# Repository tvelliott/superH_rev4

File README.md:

<html>
<b>High-performance narrow-band receiver hardware.</b>
<BR>
<BR><B>SuperH_rev4</B>
<BR>
<p>

<BR>
<BR>
<BR>

<BR>To compile:
<BR>install the gcc arm toolchain version gcc-arm-none-eabi-7-2018-q2-update/
<BR>https://developer.arm.com/tools-and-software/open-source-software/developer-tools/gnu-toolchain/gnu-rm/downloads/7-2018-q2-update
<BR>
<BR>In the firmware directory, create a symbolic link to the toolchain:
<BR>e.g. ln -s ../gcc-arm-none-eabi-7-2018-q2-update arm-toolchain
<BR>Then type 'make' 
<BR><BR>
The firmware can decode the follow protocols in stand-alone mode (NO PC):
<PRE>
Available SuperH+ built-in/stand-alone demod/decoders
------------------
FM Analog narrow/med/wide (mode fm)
AM Analog narrow/med/wide (mode am)
IQ 16-bit over UDP (mode iq) + GNURadio Driver
P25P1 Voice + Trunking Control Channel (mode p25)
DMR Voice + ConnectPlus Trunking Control Channel (mode dmr)
ADSB Mode-S - Console output (mode adsb)   This mode uses 2 separate ADCs in single ended mode with 2 Msps / 8-bit.
ACARS - Console output (mode acars)
FLEX-4FSK-1600 - Console output (mode pagers, fm)
POCSAG 1200 - Console output (mode pagers, fm)
</PRE>
<BR>
<BR>

1st IF is 1.5 GHz  (high IF like a typical spectrum analyzer)
<BR><BR>
Baseband filters are 10 - 150 kHz in 16 steps.  70dB adjacent rejection,  100+ dB alternate rejection.
<BR><BR>NCO based final tuning.
<BR><BR>20dB pre-LNA step-attenuator front-end (controlled by AGC)
<BR><BR>AGC + DSP extends dynamic range to over 150dB.
<BR><BR>ACARS receives long messages >350 miles away with an indoor antenna and 0 bit errors.
<BR><BR>DC coupling and extremely stable TCXO makes sub-Hz demodulation with software-based DC offset correction possible
<BR><BR>I/Q ADCs SNR is >= 82 dB in 16-bit differential mode of operation (10-150 kHz baseband filter mode).   

<BR>
<BR>
<a href="https://github.com/tvelliott/superH_rev4/blob/master/audio_samples/superH_fm_radio_dynamics_silence_demo.wav">superH_fm_radio_dynamics_silence_demo.wav (recorded off air)</a>
<BR>
<BR>
superH FM demod demonstration   
https://youtu.be/HBXcUFW8yaA  
<BR><BR>
P25P1 demo
https://youtu.be/G3MCHvNcKHg
<BR><BR>
superH gqrx / 40-meter / AM demo
https://youtu.be/u9L5sJRPFiQ
<BR><BR>
Local ham radio repeater VHF
https://youtu.be/9KYXXc-55yA
<BR><BR>
SuperH+ receiving ADSB
https://youtu.be/LvIR2hlR7_A
<BR><BR>
<BR>

<BR>
</html>

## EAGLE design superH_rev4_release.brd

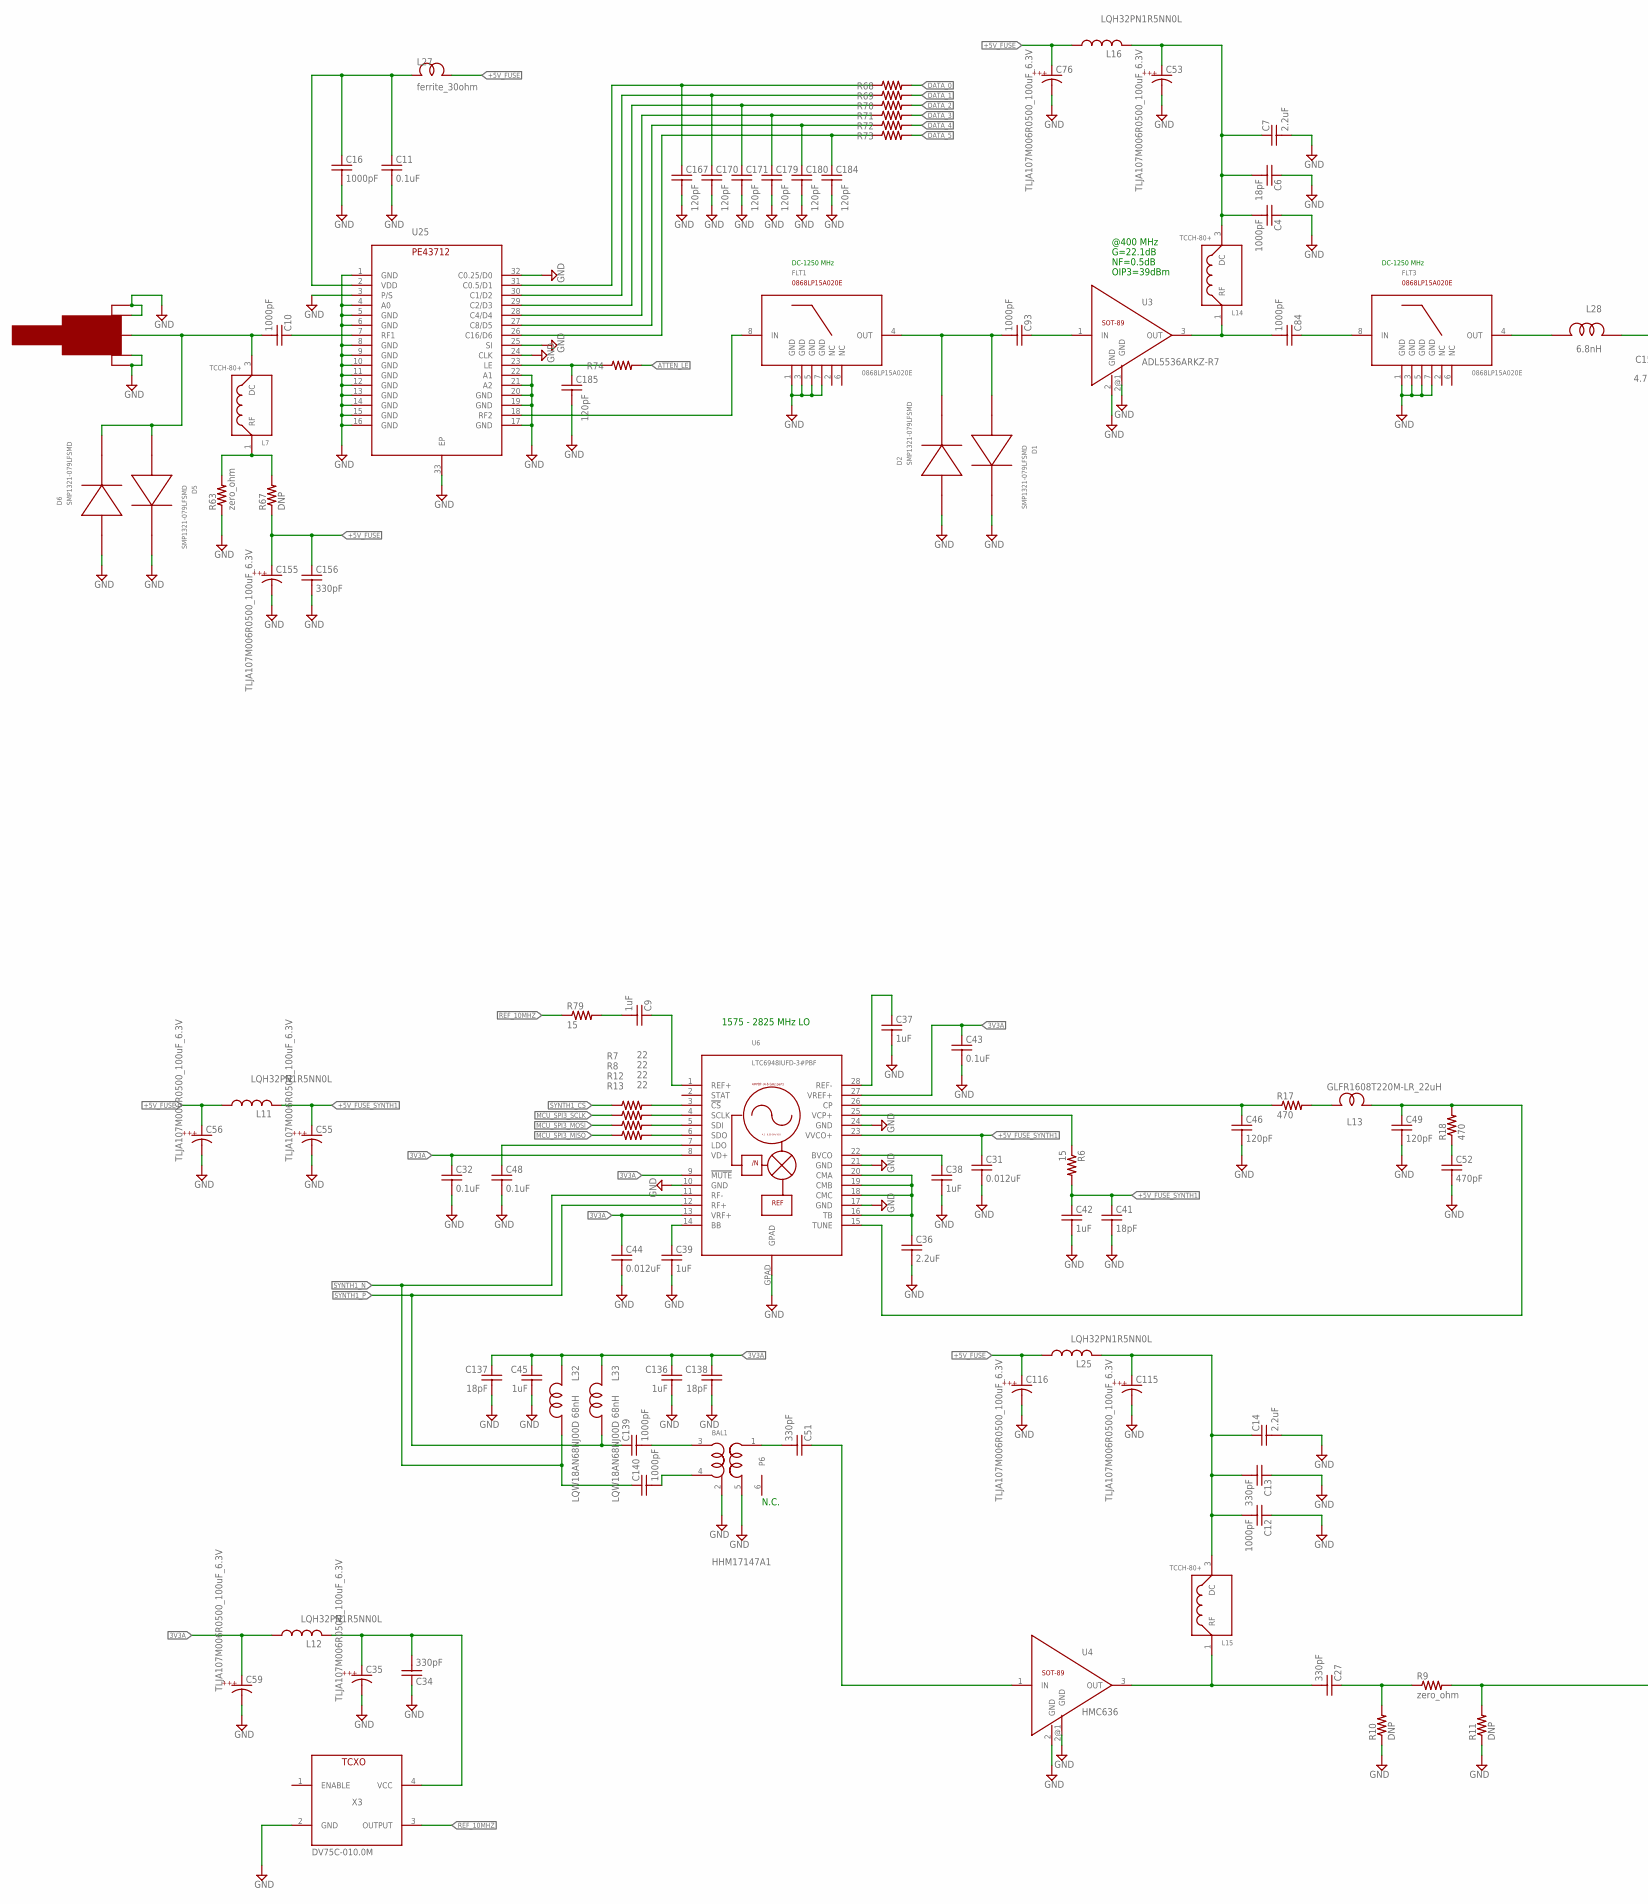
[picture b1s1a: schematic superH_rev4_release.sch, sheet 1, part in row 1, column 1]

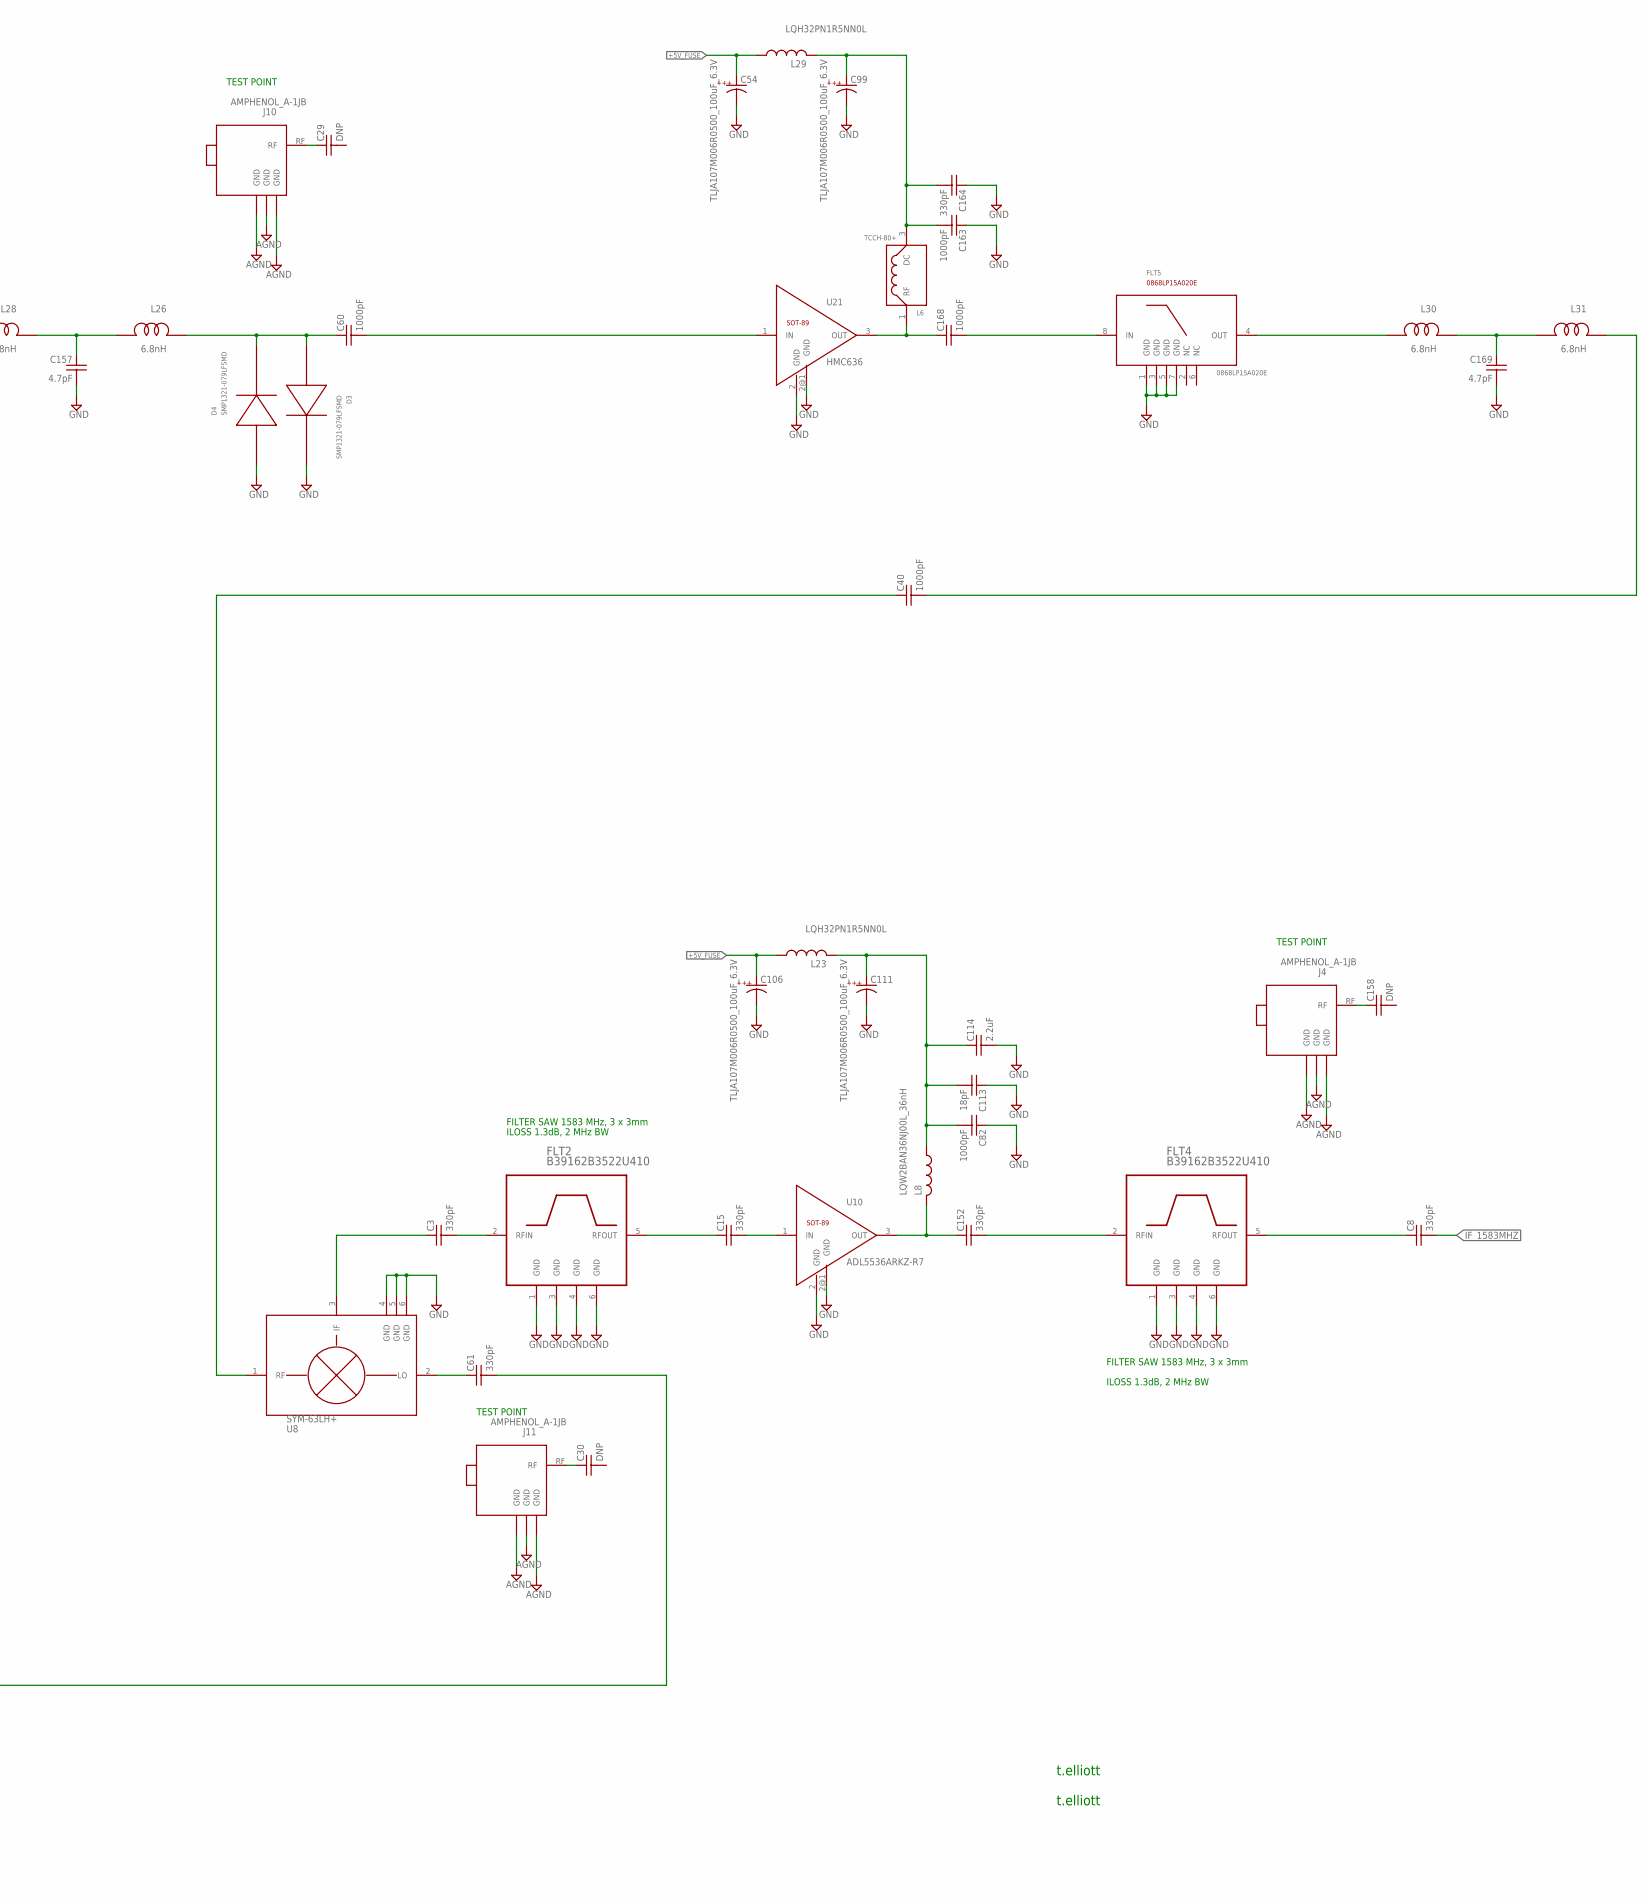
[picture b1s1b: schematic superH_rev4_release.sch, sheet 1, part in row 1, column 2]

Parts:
BAL1: HHM17147A1; TDK_BALUN_5PIN
C3, C8, C13, C15, C27, C34, C51, C61, C152, C156, C164: 330pF; C0603
C4, C10, C12, C40, C60, C82, C84, C93, C163, C168: 1000pF; C0603
C6, C113, C137, C138: 18pF; C0603
C7, C14, C36, C114: 2.2uF; C0603
C9, C45, C136: 1uF; C0603
C11, C32, C43, C48: 0.1uF; C0402
C16, C139, C140: 1000pF; C0402
C29, C30, C158: DNP; C0603
C31, C44: 0.012uF; C0402
C35, C53, C54, C55, C56, C59, C76, C99, C106, C111, C115, C116, C155: TLJA107M006R0500_100uF_6.3V; 1210K
C37, C38, C39, C42: 1uF; C0402
C41: 18pF; C0402
C46, C49, C167, C170, C171, C179, C180, C184, C185: 120pF; C0402
C52: 470pF; C0402
C157, C169: 4.7pF; C0603
D1, D2, D3, D4, D5, D6: SMP1321-079LFSMD; SC-79_PINDIODE
FLT1, FLT3, FLT5: 0868LP15A020E; LPF_0868LP15A020
FLT2, FLT4: B39162B3522U410; SM3030-6
J3: SMA0.062; SMA_EDGE
J4, J10, J11: AMPHENOL_A-1JB; UFLCONNECTOR
L6, L7, L14, L15: TCCH-80+
L8: LQW2BAN36NJ00L_36nH; L2012C; PARTNUMBER ELJ-PA331KF
L11, L12, L16, L23, L25, L29: LQH32PN1R5NN0L; L3225M; PARTNUMBER ELJ-PA331KF
L13: GLFR1608T220M-LR_22uH; 0603
L26, L28, L30, L31: 6.8nH; MURATA_LQW_0603
L27: ferrite_30ohm; 0603
L32, L33: LQW18AN68NJ00D 68nH; MURATA_LQW_0603
R6, R68, R69, R70, R71, R72, R73, R74, R79: 15; R0402
R7, R8, R12, R13: 22; R0603_COMPACT
R9: zero_ohm; R0603
R10, R11: DNP; R0603
R17, R18: 470; R0402
R63: zero_ohm; R1206
R67: DNP; R1206
U3, U10: ADL5536ARKZ-R7; SOT89
U4, U21: HMC636; SOT89
U6: LTC6948IUFD-3#PBF; QFN28_NONSQ
U8: SYM-63LH+; SYM-18H
U25: PE43712SMD; QFN32
X3: DV75C-010.0M; CWX8XX_5MM_7MM

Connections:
3V3A: C32.1, C43.1, C44.1, C45.1, C59.A, C136.1, C137.1, C138.1, L12.1, L32.2, L33.2, U6.8 (VD+), U6.9 (!MUTE), U6.13 (VRF+), U6.27 (VREF+); also elsewhere on the board
+5V_ATTEN: C11.1, C16.1, L27.1, U25.2 (VDD)
+5V_FUSE: C54.A, C56.A, C76.A, C106.A, C116.A, C155.A, C156.1, L11.1, L16.1, L23.1, L25.1, L27.2, L29.1, R67.1; also elsewhere on the board
+5V_FUSE_SYNTH1: C31.1, C41.1, C42.1, C55.A, L11.2, R6.2, U6.23 (VVCO+)
ATTEN_LE: R74.2; also elsewhere on the board
BALUN_N: BAL1.4 (BP1), C140.2
BALUN_P: BAL1.3 (BP2), C139.2
D0: C167.1, R68.1, U25.31 (C0.5/D1)
D1: C170.1, R69.1, U25.30 (C1/D2)
D2: C171.1, R70.1, U25.29 (C2/D3)
D3: C179.1, R71.1, U25.28 (C4/D4)
D4: C180.1, R72.1, U25.27 (C8/D5)
D5: C184.1, R73.1, U25.26 (C16/D6)
DATA_0: R68.2; also elsewhere on the board
DATA_1: R69.2; also elsewhere on the board
DATA_2: R70.2; also elsewhere on the board
DATA_3: R71.2; also elsewhere on the board
DATA_4: R72.2; also elsewhere on the board
DATA_5: R73.2; also elsewhere on the board
GND: BAL1.2 (FEED), BAL1.5 (GND), C4.1, C6.1, C7.2, C11.2, C12.1, C13.1, C14.2, C16.2, C31.2, C32.2, C34.1, C35.C, C36.2, C37.2, C38.2, C39.2, C41.2, C42.2, C43.2, C44.2, C45.2, C46.2, C48.2, C49.2, C52.2, C53.C, C54.C, C55.C, C56.C, C59.C, C76.C, C82.1, C99.C, C106.C, C111.C, C113.1, C114.2, C115.C, C116.C, C136.2, C137.2, C138.2, C155.C, C156.2, C157.2, C163.1, C164.1, C167.2, C169.2, C170.2, C171.2, C179.2, C180.2, C184.2, C185.2, D1.C, D2.A, D3.C, D4.A, D5.C, D6.A, FLT1.1 (GND), FLT1.3 (GND), FLT1.5 (GND), FLT1.7 (GND), FLT2.1 (GND), FLT2.3 (GND), FLT2.4 (GND), FLT2.6 (GND), FLT3.1 (GND), FLT3.3 (GND), FLT3.5 (GND), FLT3.7 (GND), FLT4.1 (GND), FLT4.3 (GND), FLT4.4 (GND), FLT4.6 (GND), FLT5.1 (GND), FLT5.3 (GND), FLT5.5 (GND), FLT5.7 (GND), J3.GND@1 (GND), J3.GND@2 (GND), J3.GND@3 (GND), J3.GND@4 (GND), J4.1 (GND), J4.2 (GND), J4.3 (GND), J10.1 (GND), J10.2 (GND), J10.3 (GND), J11.1 (GND), J11.2 (GND), J11.3 (GND), R10.1, R11.1, R63.1, U3.2 (GND), U3.2@1 (GND), U4.2 (GND), U4.2@1 (GND), U6.10 (GND), U6.17 (GND), U6.21 (GND), U6.24 (GND), U6.GPAD, U8.4 (GND), U8.5 (GND), U8.6 (GND), U10.2 (GND), U10.2@1 (GND), U21.2 (GND), U21.2@1 (GND), U25.1 (GND), U25.3 (P/S), U25.4 (A0), U25.5 (GND), U25.6 (GND), U25.8 (GND), U25.9 (GND), U25.10 (GND), U25.11 (GND), U25.12 (GND), U25.13 (GND), U25.14 (GND), U25.15 (GND), U25.16 (GND), U25.17 (GND), U25.19 (GND), U25.20 (GND), U25.21 (A2), U25.22 (A1), U25.24 (CLK), U25.25 (SI), U25.32 (C0.25/D0), U25.33 (EP), X3.2 (GND); also elsewhere on the board
IF_1583MHZ: C8.2; also elsewhere on the board
LE: C185.1, R74.1, U25.23 (LE)
MCU_SPI3_MISO: R13.1; also elsewhere on the board
MCU_SPI3_MOSI: R12.1; also elsewhere on the board
MCU_SPI3_SCLK: R8.1; also elsewhere on the board
unnamed: C152.2, FLT4.2 (RFIN)
unnamed: C84.2, L14.1 (RF), U3.3 (OUT)
unnamed: C82.2, C111.A, C113.2, C114.1, L8.1, L23.2
unnamed: C60.1, D3.A, D4.C, L26.2
unnamed: C27.2, L15.1 (RF), U4.3 (OUT)
unnamed: C29.1, J10.RF
unnamed: C30.1, J11.RF
unnamed: C15.1, FLT2.5 (RFOUT)
unnamed: C3.2, FLT2.2 (RFIN)
unnamed: C51.1, U4.1 (IN)
unnamed: C15.2, U10.1 (IN)
unnamed: C9.1, U6.1 (REF+)
unnamed: C27.1, R9.1, R10.2
unnamed: C61.2, R9.2, R11.2
unnamed: C4.2, C6.2, C7.1, C53.A, L14.3 (DC), L16.2
unnamed: C8.1, FLT4.5 (RFOUT)
unnamed: FLT1.8 (IN), U25.18 (RF2)
unnamed: C99.A, C163.2, C164.2, L6.3 (DC), L29.2
unnamed: C37.1, U6.28 (REF-)
unnamed: C36.1, U6.16 (TB), U6.18 (CMC), U6.19 (CMB), U6.20 (CMA)
unnamed: C38.1, U6.22 (BVCO)
unnamed: C39.1, U6.14 (BB)
unnamed: R6.1, U6.25 (VCP+)
unnamed: C48.1, U6.7 (LDO)
unnamed: C46.1, R17.1, U6.26 (CP)
unnamed: C61.1, U8.2 (LO)
unnamed: C93.1, U3.1 (IN)
unnamed: BAL1.1 (UBAL), C51.2
unnamed: C52.1, R18.1
unnamed: C49.1, L13.2, R18.2, U6.15 (TUNE)
unnamed: L13.1, R17.2
unnamed: C93.2, D1.A, D2.C, FLT1.4 (OUT)
unnamed: R7.2, U6.3 (!CS)
unnamed: R8.2, U6.4 (SCLK)
unnamed: R12.2, U6.5 (SDI)
unnamed: R13.2, U6.6 (SDO)
unnamed: C34.2, C35.A, L12.2, X3.4 (VCC)
unnamed: C3.1, U8.3 (IF)
unnamed: C157.1, L26.1, L28.2
unnamed: FLT3.4 (OUT), L28.1
unnamed: L7.1 (RF), R63.2, R67.2
unnamed: C152.1, L8.2, U10.3 (OUT)
unnamed: C84.1, FLT3.8 (IN)
unnamed: C158.1, J4.RF
unnamed: C60.2, U21.1 (IN)
unnamed: C168.1, L6.1 (RF), U21.3 (OUT)
unnamed: C40.1, U8.1 (RF)
unnamed: FLT5.4 (OUT), L30.1
unnamed: C169.1, L30.2, L31.1
unnamed: C168.2, FLT5.8 (IN)
unnamed: C40.2, L31.2
unnamed: C10.1, U25.7 (RF1)
unnamed: C10.2, D5.A, D6.C, J3.RF, L7.3 (DC)
unnamed: C9.2, R79.2
unnamed: C12.2, C13.2, C14.1, C115.A, L15.3 (DC), L25.2
REF_10MHZ: R79.1, X3.3 (OUTPUT); also elsewhere on the board
SYNTH1_CS: R7.1; also elsewhere on the board
SYNTH1_N: C140.1, L32.1, U6.11 (RF-)
SYNTH1_P: C139.1, L33.1, U6.12 (RF+)

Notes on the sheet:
t.elliott
TEST POINT
G=22.1dB
NF=0.5dB
OIP3=39dBm
FILTER SAW 1583 MHz, 3 x 3mm
N.C.
1575 - 2825 MHz LO
ILOSS 1.3dB, 2 MHz BW
DC-1250 MHz
@400 MHz

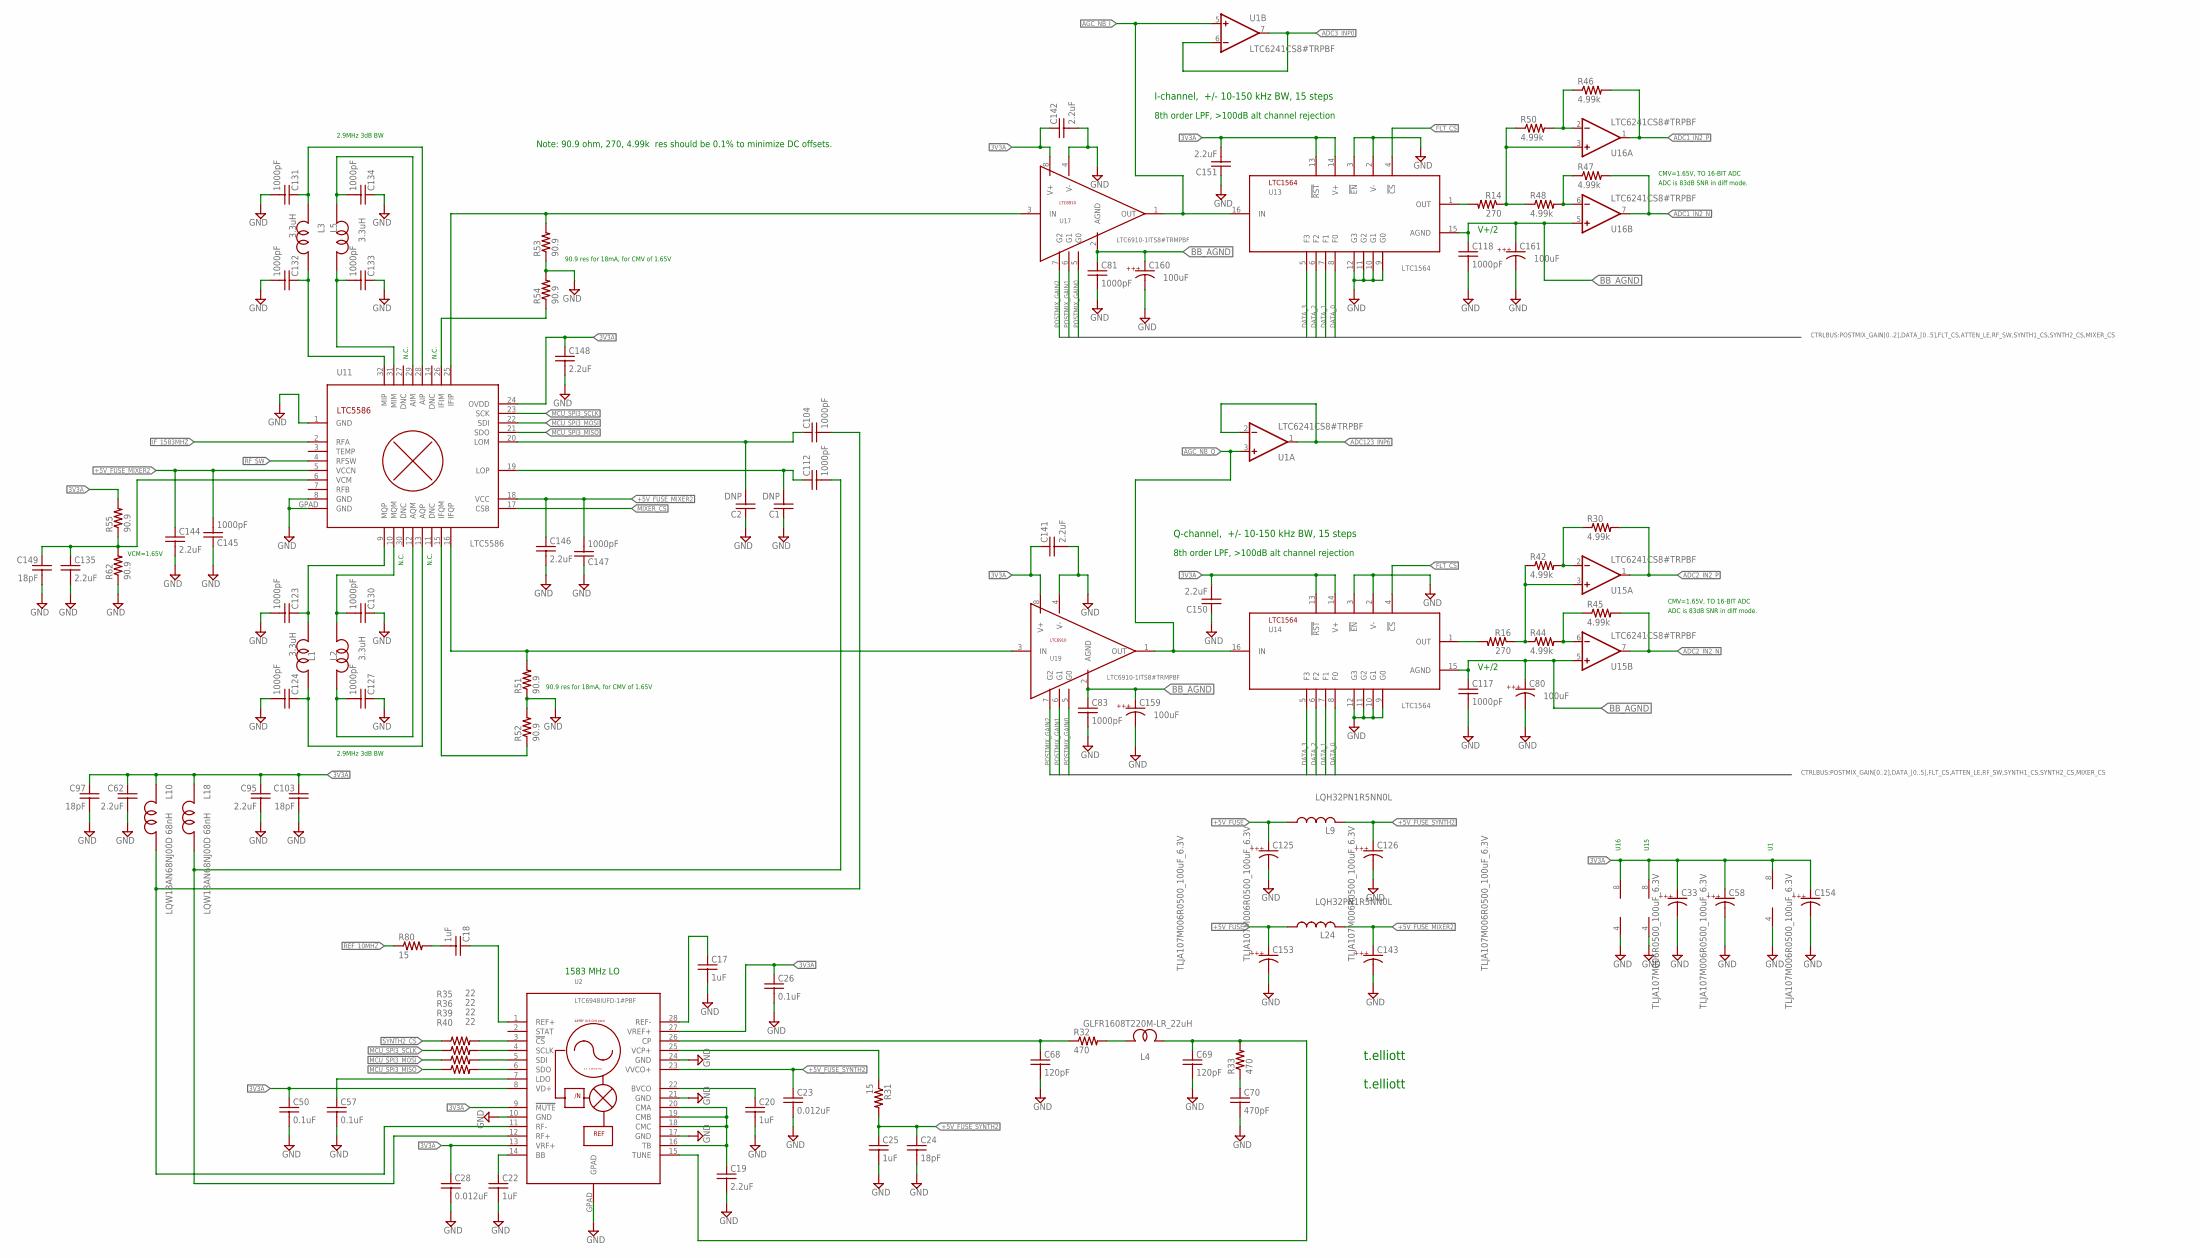
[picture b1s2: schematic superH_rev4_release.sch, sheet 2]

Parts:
C1, C2: DNP; C0402
C17, C20, C22, C25: 1uF; C0402
C18: 1uF; C0603
C19, C62, C95, C135: 2.2uF; C0603
C23, C28: 0.012uF; C0402
C24: 18pF; C0402
C26, C50, C57: 0.1uF; C0402
C33, C58, C125, C126, C143, C153, C154: TLJA107M006R0500_100uF_6.3V; 1210K
C68, C69: 120pF; C0402
C70: 470pF; C0402
C80, C159, C160, C161: 100uF; 1210K
C81, C83, C117, C118, C123, C124, C127, C130, C131, C132, C133, C134: 1000pF; C0603
C97, C103, C149: 18pF; C0603
C104, C112, C145, C147: 1000pF; C0402
C141, C142, C144, C146, C148, C150, C151: 2.2uF; C0402
L1, L2, L3, L5: 3.3uH; MURATA_LQW_0603
L4: GLFR1608T220M-LR_22uH; 0603
L9, L24: LQH32PN1R5NN0L; L3225M; PARTNUMBER ELJ-PA331KF
L10, L18: LQW18AN68NJ00D 68nH; MURATA_LQW_0603
R14, R16: 270; R0603
R30, R42, R44, R45, R46, R47, R48, R50: 4.99k; R0402
R31, R80: 15; R0402
R32, R33: 470; R0402
R35, R36, R39, R40: 22; R0603_COMPACT
R51, R52, R53, R54, R55, R62: 90.9; R0402
U1, U15, U16: LTC6241CS8#TRPBF; SO08
U2: LTC6948IUFD-1#PBF; QFN28_NONSQ
U11: LTC5586; QFN32
U13, U14: LTC1564; SSOP16
U17, U19: LTC6910-1ITS8#TRMPBF; TSOT-23-8

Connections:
3V3A: C26.1, C28.1, C33.A, C50.1, C58.A, C62.1, C95.1, C97.1, C103.1, C141.1, C142.1, C148.1, C150.2, C151.2, C154.A, L10.2, L18.2, R55.2, U1.8 (V+), U2.8 (VD+), U2.9 (!MUTE), U2.13 (VRF+), U2.27 (VREF+), U11.24 (OVDD), U13.13 (!RST), U13.14 (V+), U14.13 (!RST), U14.14 (V+), U15.8 (V+), U16.8 (V+), U17.8 (V+), U19.8 (V+); also elsewhere on the board
+5V_FUSE: C125.A, C153.A, L9.1, L24.1; also elsewhere on the board
+5V_FUSE_MIXER2: C143.A, C144.1, C145.2, C146.1, C147.2, L24.2, U11.5 (VCCN), U11.18 (VCC)
+5V_FUSE_SYNTH2: C23.1, C24.1, C25.1, C126.A, L9.2, R31.2, U2.23 (VVCO+)
ADC1_IN2_N: R47.2, U16.7 (OUT); also elsewhere on the board
ADC1_IN2_P: R46.2, U16.1 (OUT); also elsewhere on the board
ADC2_IN2_N: R45.2, U15.7 (OUT); also elsewhere on the board
ADC2_IN2_P: R30.2, U15.1 (OUT); also elsewhere on the board
ADC3_INP0: U1.6 (-IN), U1.7 (OUT); also elsewhere on the board
ADC123_INP6: U1.1 (OUT), U1.2 (-IN); also elsewhere on the board
AGC_NB_I: U1.5 (+IN), U13.16 (IN), U17.1 (OUT)
AGC_NB_Q: U1.3 (+IN), U14.16 (IN), U19.1 (OUT)
BB_AGND: C80.A, C81.1, C83.1, C117.1, C118.1, C159.A, C160.A, C161.A, U13.15 (AGND), U14.15 (AGND), U15.5 (+IN), U16.5 (+IN), U17.2 (AGND), U19.2 (AGND)
DATA_0: U13.8 (F0), U14.8 (F0); also elsewhere on the board
DATA_1: U13.7 (F1), U14.7 (F1); also elsewhere on the board
DATA_2: U13.6 (F2), U14.6 (F2); also elsewhere on the board
DATA_3: U13.5 (F3), U14.5 (F3); also elsewhere on the board
FLT_CS: U13.4 (!CS), U14.4 (!CS); also elsewhere on the board
GND: C1.1, C2.1, C17.2, C19.2, C20.2, C22.2, C23.2, C24.2, C25.2, C26.2, C28.2, C33.C, C50.2, C57.2, C58.C, C62.2, C68.2, C69.2, C70.2, C80.C, C81.2, C83.2, C95.2, C97.2, C103.2, C117.2, C118.2, C123.2, C124.2, C125.C, C126.C, C127.1, C130.1, C131.2, C132.2, C133.1, C134.1, C135.2, C141.2, C142.2, C143.C, C144.2, C145.1, C146.2, C147.1, C148.2, C149.2, C150.1, C151.1, C153.C, C154.C, C159.C, C160.C, C161.C, R51.1, R52.2, R53.1, R54.2, R62.1, U1.4 (V-), U2.10 (GND), U2.17 (GND), U2.21 (GND), U2.24 (GND), U2.GPAD, U11.1 (GND), U11.8 (GND), U11.GPAD (GND), U13.2 (V-), U13.3 (!EN), U13.9 (G0), U13.10 (G1), U13.11 (G2), U13.12 (G3), U14.2 (V-), U14.3 (!EN), U14.9 (G0), U14.10 (G1), U14.11 (G2), U14.12 (G3), U15.4 (V-), U16.4 (V-), U17.4 (V-), U19.4 (V-); also elsewhere on the board
IFI_N: R54.1, U11.26 (IFIM)
IFI_P: R53.2, U11.25 (IFIP), U17.3 (IN)
IFQ_N: R52.1, U11.15 (IFQM)
IFQ_P: R51.2, U11.16 (IFQP), U19.3 (IN)
IF_1583MHZ: U11.2 (RFA); also elsewhere on the board
LO_N: C2.2, C104.1, U11.20 (LOM)
LO_P: C1.2, C112.1, U11.19 (LOP)
MCU_SPI3_MISO: R40.1, U11.21 (SDO); also elsewhere on the board
MCU_SPI3_MOSI: R39.1, U11.22 (SDI); also elsewhere on the board
MCU_SPI3_SCLK: R36.1, U11.23 (SCK); also elsewhere on the board
MIXER_CS: U11.17 (CSB); also elsewhere on the board
unnamed: C18.1, U2.1 (REF+)
unnamed: C17.1, U2.28 (REF-)
unnamed: C19.1, U2.16 (TB), U2.18 (CMC), U2.19 (CMB), U2.20 (CMA)
unnamed: C20.1, U2.22 (BVCO)
unnamed: C22.1, U2.14 (BB)
unnamed: R31.1, U2.25 (VCP+)
unnamed: C57.1, U2.7 (LDO)
unnamed: C68.1, R32.1, U2.26 (CP)
unnamed: C70.1, R33.1
unnamed: C69.1, L4.2, R33.2, U2.15 (TUNE)
unnamed: L4.1, R32.2
unnamed: R35.2, U2.3 (!CS)
unnamed: R36.2, U2.4 (SCLK)
unnamed: R39.2, U2.5 (SDI)
unnamed: R40.2, U2.6 (SDO)
unnamed: R47.1, R48.2, U16.6 (-IN)
unnamed: R30.1, R42.2, U15.2 (-IN)
unnamed: R44.2, R45.1, U15.6 (-IN)
unnamed: R16.1, R42.1, R44.1, U15.3 (+IN)
unnamed: R16.2, U14.1 (OUT)
unnamed: R14.2, U13.1 (OUT)
unnamed: R46.1, R50.2, U16.2 (-IN)
unnamed: R14.1, R48.1, R50.1, U16.3 (+IN)
unnamed: C130.2, L2.1, U11.10 (MQM)
unnamed: C123.1, L1.2, U11.9 (MQP)
unnamed: C127.2, L2.2, U11.12 (AQM)
unnamed: C124.1, L1.1, U11.13 (AQP)
unnamed: C133.2, L5.2, U11.31 (MIM)
unnamed: C132.1, L3.1, U11.32 (MIP)
unnamed: C131.1, L3.2, U11.28 (AIP)
unnamed: C134.2, L5.1, U11.29 (AIM)
unnamed: C135.1, C149.1, R55.1, R62.2, U11.6 (VCM)
unnamed: C18.2, R80.2
POSTMIX_GAIN0: U17.5 (G0), U19.5 (G0); also elsewhere on the board
POSTMIX_GAIN1: U17.6 (G1), U19.6 (G1); also elsewhere on the board
POSTMIX_GAIN2: U17.7 (G2), U19.7 (G2); also elsewhere on the board
REF_10MHZ: R80.1; also elsewhere on the board
RF_SW: U11.4 (RFSW); also elsewhere on the board
SYNTH2_CS: R35.1; also elsewhere on the board
SYNTH2_N: C104.2, L10.1, U2.11 (RF-)
SYNTH2_P: C112.2, L18.1, U2.12 (RF+)

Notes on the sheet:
t.elliott
1583 MHz LO
V+/2
CMV=1.65V, TO 16-BIT ADC
8th order LPF, >100dB alt channel rejection
ADC is 83dB SNR in diff mode.
N.C.
90.9 res for 18mA, for CMV of 1.65V
VCM=1.65V
2.9MHz 3dB BW
Q-channel, +/- 10-150 kHz BW, 15 steps
I-channel, +/- 10-150 kHz BW, 15 steps
U16
U15
Note: 90.9 ohm, 270, 4.99k res should be 0.1% to minimize DC offsets.

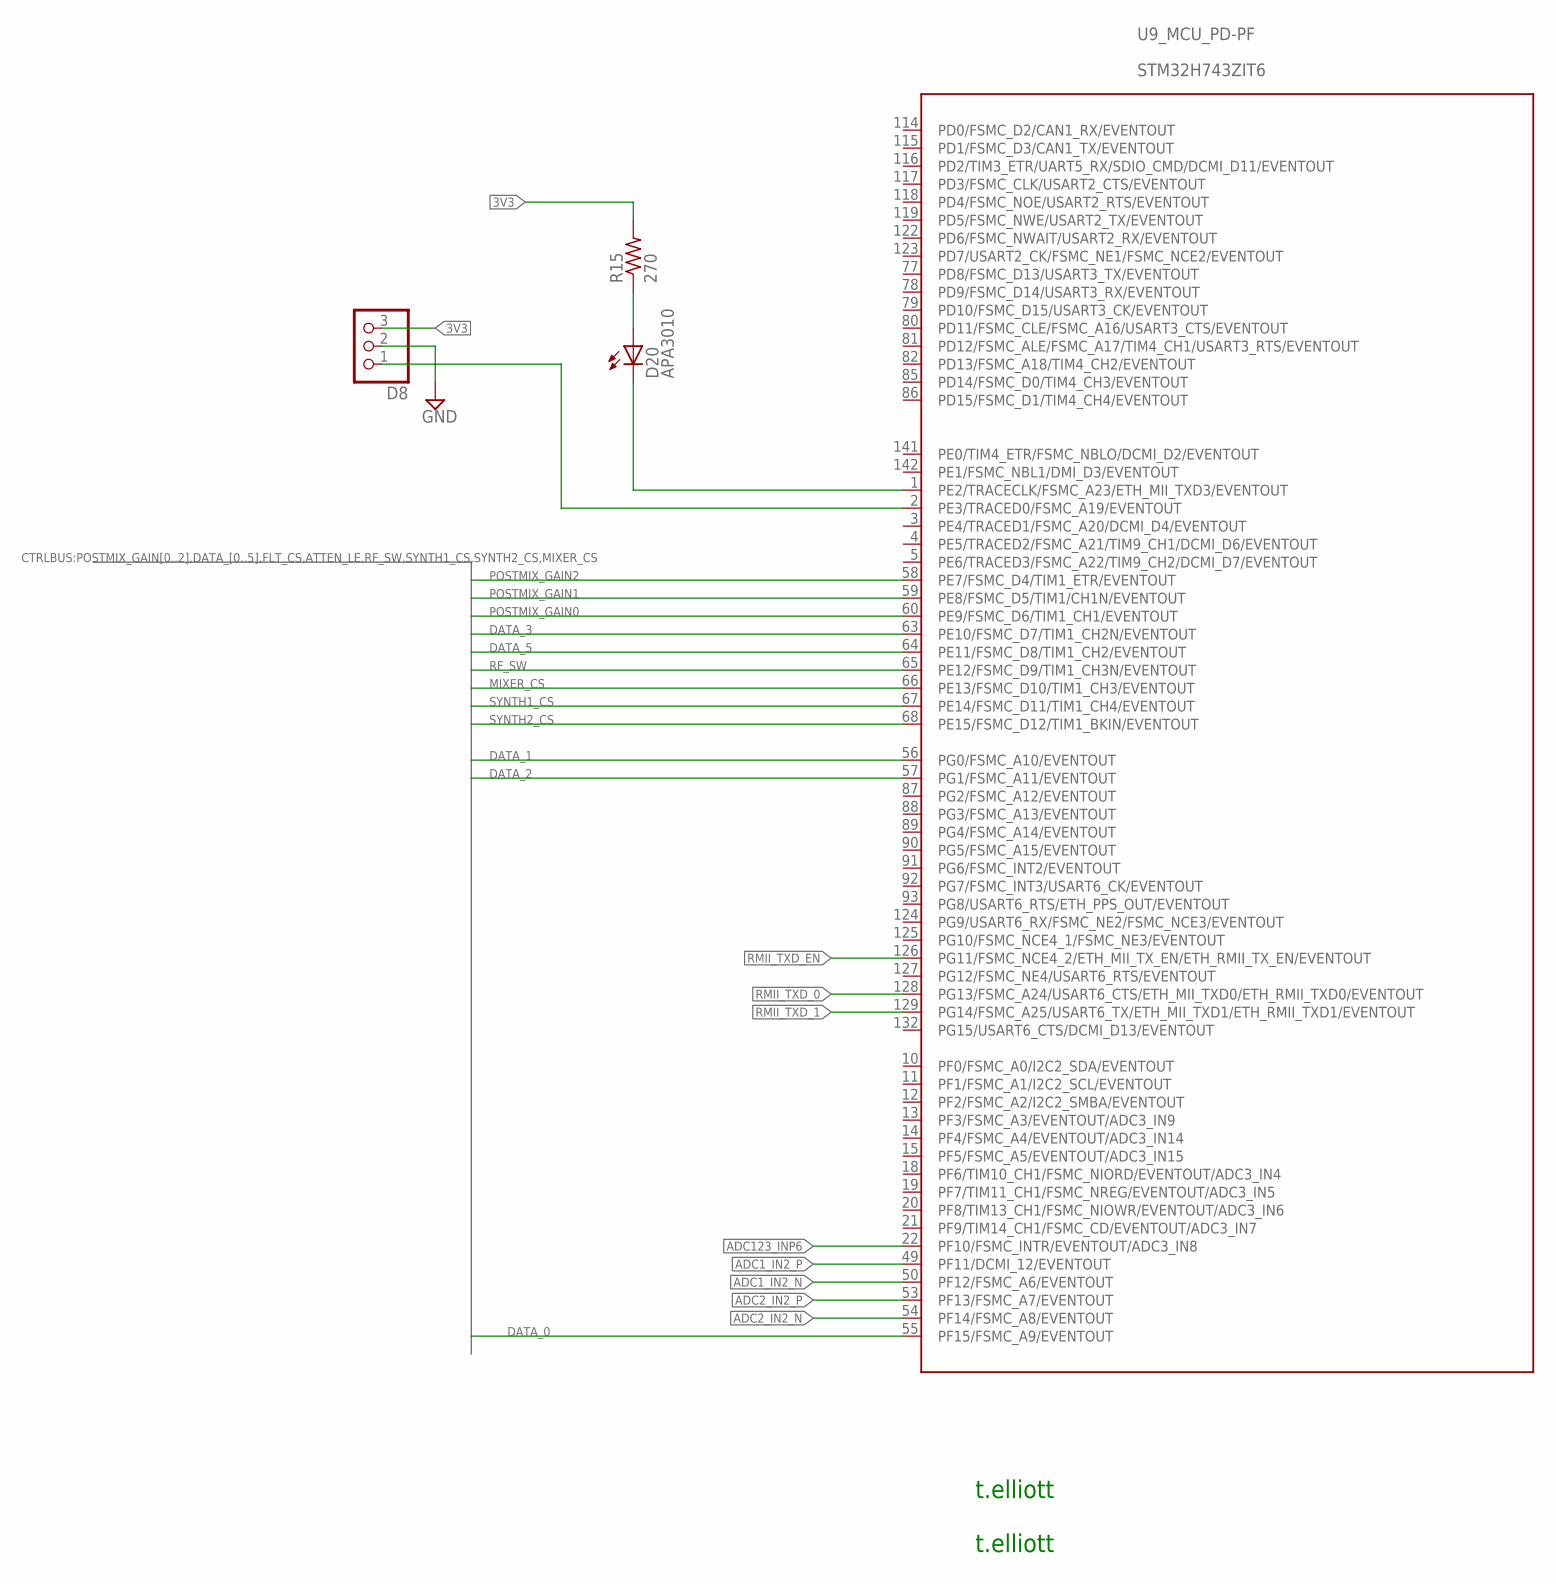
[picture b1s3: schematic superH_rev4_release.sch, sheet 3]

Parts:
D8: PINHD-1X3; 1X03
D20: APA3010; LED-APA3010_1PRIMARY
R15: 270; R0603
U9: STM32H743ZIT6; STM32F407_144

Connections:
3V3: D8.3, R15.2; also elsewhere on the board
ADC1_IN2_N: U9.50 (PF12/FSMC_A6/EVENTOUT); also elsewhere on the board
ADC1_IN2_P: U9.49 (PF11/DCMI_12/EVENTOUT); also elsewhere on the board
ADC2_IN2_N: U9.54 (PF14/FSMC_A8/EVENTOUT); also elsewhere on the board
ADC2_IN2_P: U9.53 (PF13/FSMC_A7/EVENTOUT); also elsewhere on the board
ADC123_INP6: U9.22 (PF10/FSMC_INTR/EVENTOUT/ADC3_IN8); also elsewhere on the board
DATA_0: U9.55 (PF15/FSMC_A9/EVENTOUT); also elsewhere on the board
DATA_1: U9.56 (PG0/FSMC_A10/EVENTOUT); also elsewhere on the board
DATA_2: U9.57 (PG1/FSMC_A11/EVENTOUT); also elsewhere on the board
DATA_3: U9.63 (PE10/FSMC_D7/TIM1_CH2N/EVENTOUT); also elsewhere on the board
DATA_5: U9.64 (PE11/FSMC_D8/TIM1_CH2/EVENTOUT); also elsewhere on the board
GND: D8.2; also elsewhere on the board
MIXER_CS: U9.66 (PE13/FSMC_D10/TIM1_CH3/EVENTOUT); also elsewhere on the board
unnamed: D20.1 (C), U9.1 (PE2/TRACECLK/FSMC_A23/ETH_MII_TXD3/EVEN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)
unnamed: D8.1, U9.2 (PE3/TRACED0/FSMC_A19/EVENTOUT)
unnamed: D20.2 (A), R15.1
POSTMIX_GAIN0: U9.60 (PE9/FSMC_D6/TIM1_CH1/EVENTOUT); also elsewhere on the board
POSTMIX_GAIN1: U9.59 (PE8/FSMC_D5/TIM1/CH1N/EVENTOUT); also elsewhere on the board
POSTMIX_GAIN2: U9.58 (PE7/FSMC_D4/TIM1_ETR/EVENTOUT); also elsewhere on the board
RF_SW: U9.65 (PE12/FSMC_D9/TIM1_CH3N/EVENTOUT); also elsewhere on the board
RMII_TXD_0: U9.128 (PG13/FSMC_A24/USART6_CTS/ETH_MII_TXD0/E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); also elsewhere on the board
RMII_TXD_1: U9.129 (PG14/FSMC_A25/USART6_TX/ETH_MII_TXD1/ET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); also elsewhere on the board
RMII_TXD_EN: U9.126 (PG11/FSMC_NCE4_2/ETH_MII_TX_EN/ETH_RMII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); also elsewhere on the board
SYNTH1_CS: U9.67 (PE14/FSMC_D11/TIM1_CH4/EVENTOUT); also elsewhere on the board
SYNTH2_CS: U9.68 (PE15/FSMC_D12/TIM1_BKIN/EVENTOUT); also elsewhere on the board

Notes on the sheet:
t.elliott

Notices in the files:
firmware/ethernetif.c:
Copyright (c) 2018 STMicroelectronics International N.V.
All rights reserved.
(C) COPYRIGHT STMicroelectronics *****END OF FILE
firmware/stm32h7xx_hal_msp.c:
© Copyright (c) 2019 STMicroelectronics.
This software component is licensed by ST under BSD 3-Clause license,
the "License"; You may not use this file except in compliance with the
License. You may obtain a copy of the License at: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
parts and their libraries:
cirrus-3: Copyright (C) 2005 by Bob Starr, rtzaudio@mindspring.com
